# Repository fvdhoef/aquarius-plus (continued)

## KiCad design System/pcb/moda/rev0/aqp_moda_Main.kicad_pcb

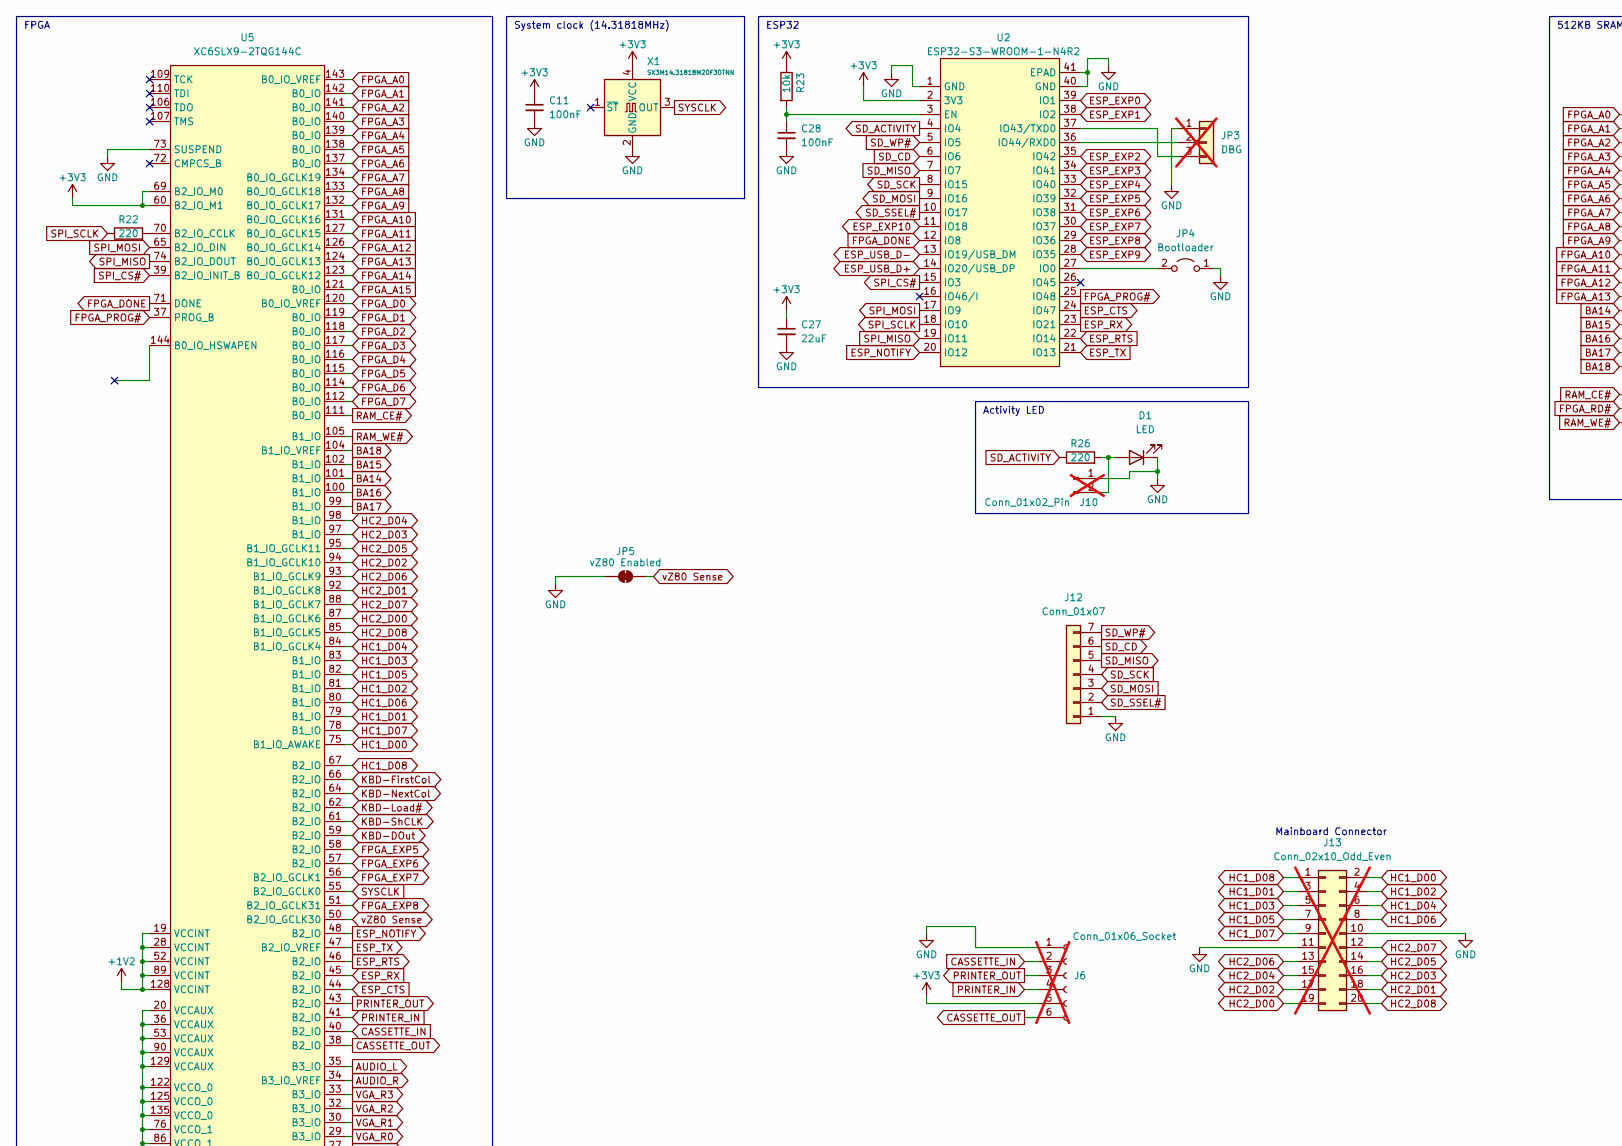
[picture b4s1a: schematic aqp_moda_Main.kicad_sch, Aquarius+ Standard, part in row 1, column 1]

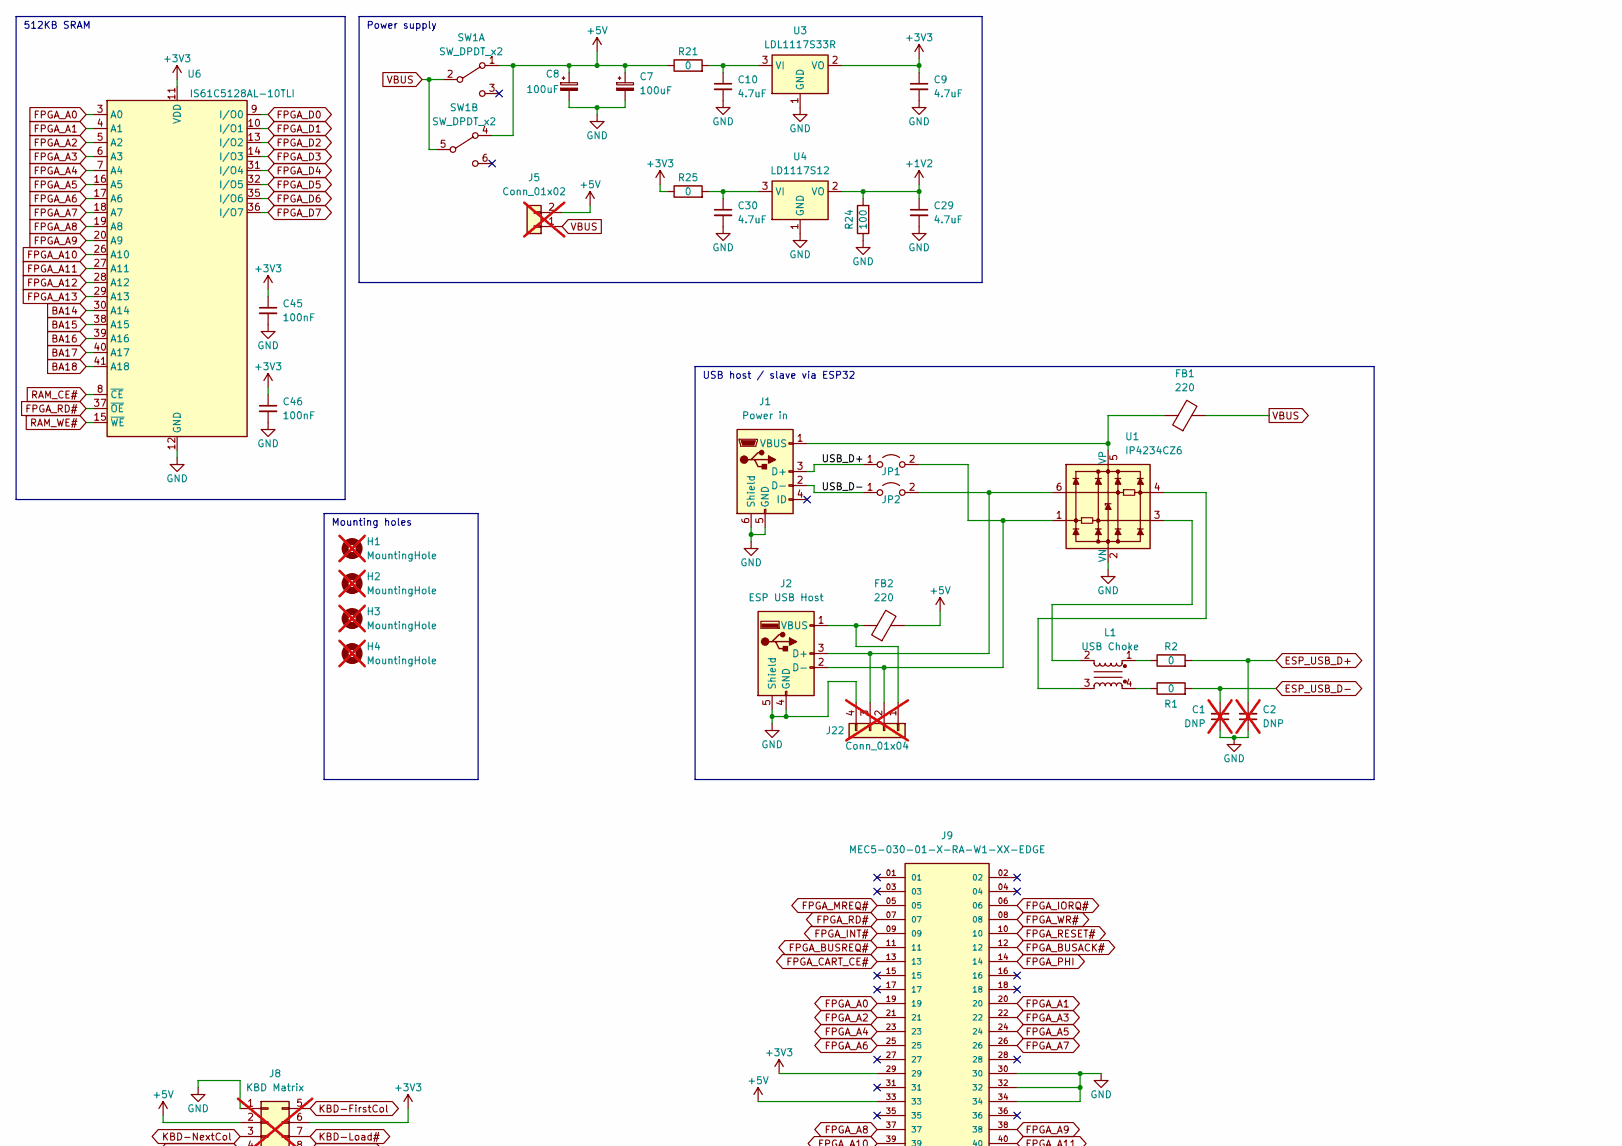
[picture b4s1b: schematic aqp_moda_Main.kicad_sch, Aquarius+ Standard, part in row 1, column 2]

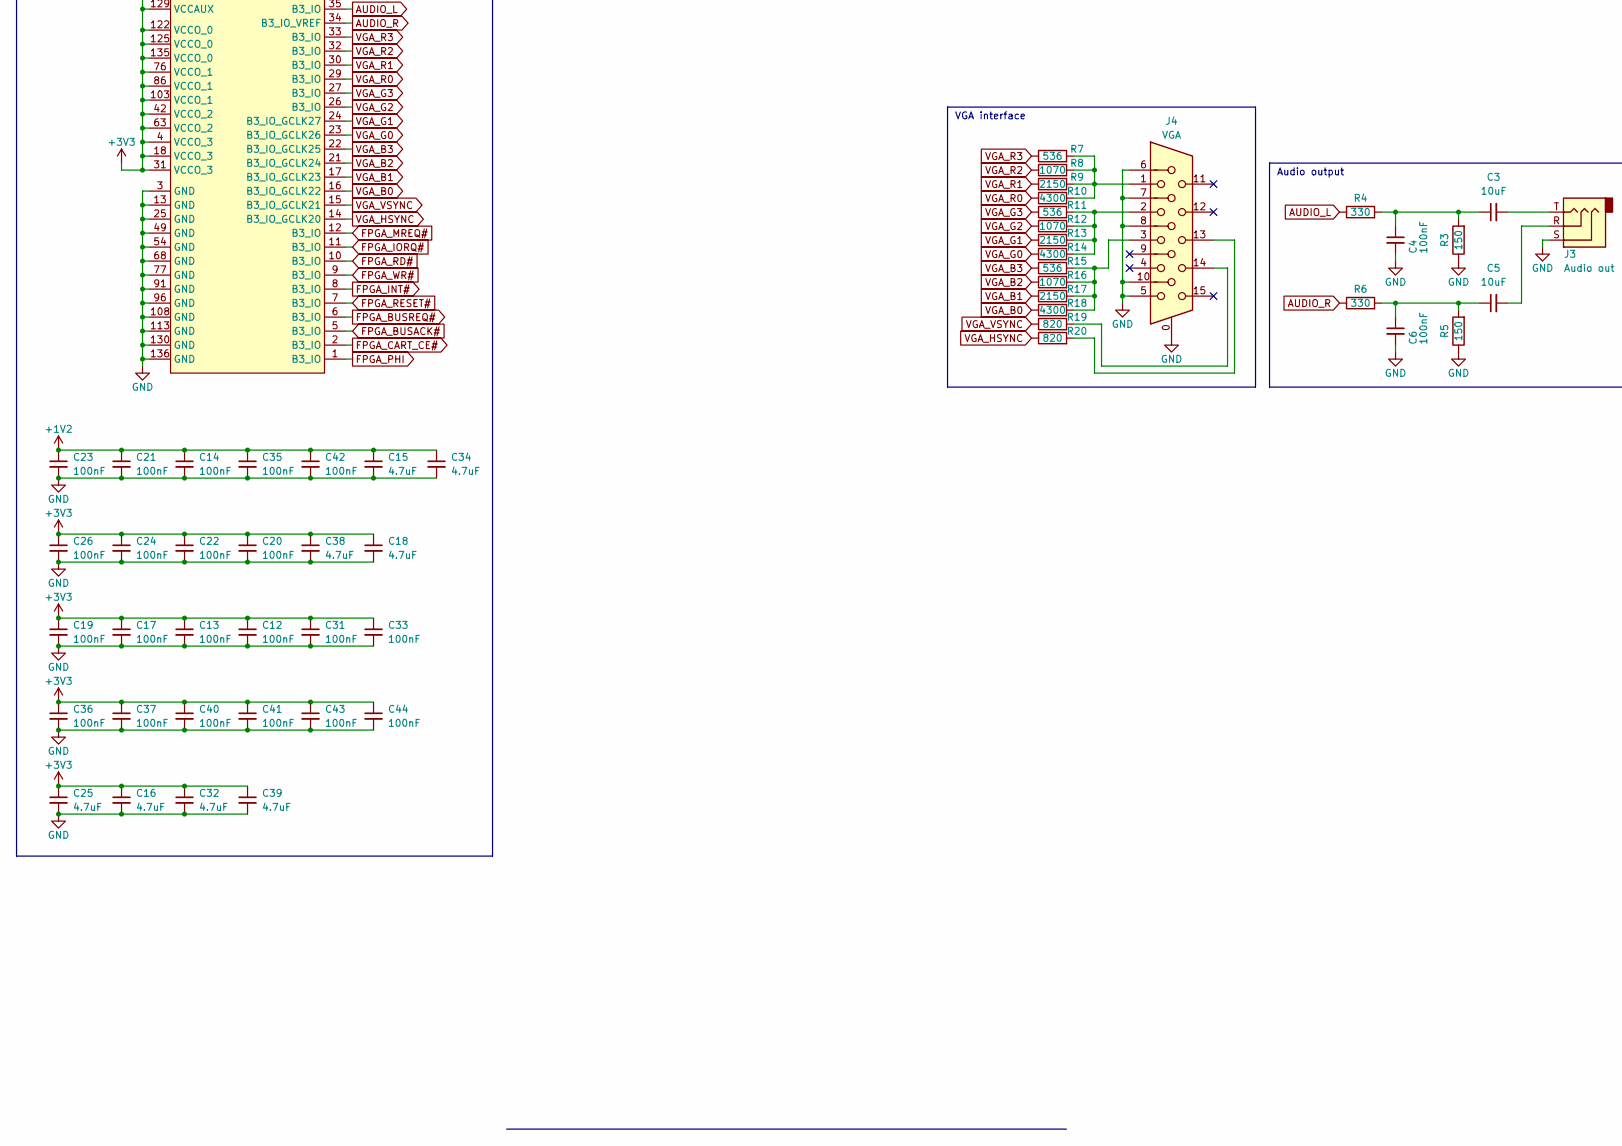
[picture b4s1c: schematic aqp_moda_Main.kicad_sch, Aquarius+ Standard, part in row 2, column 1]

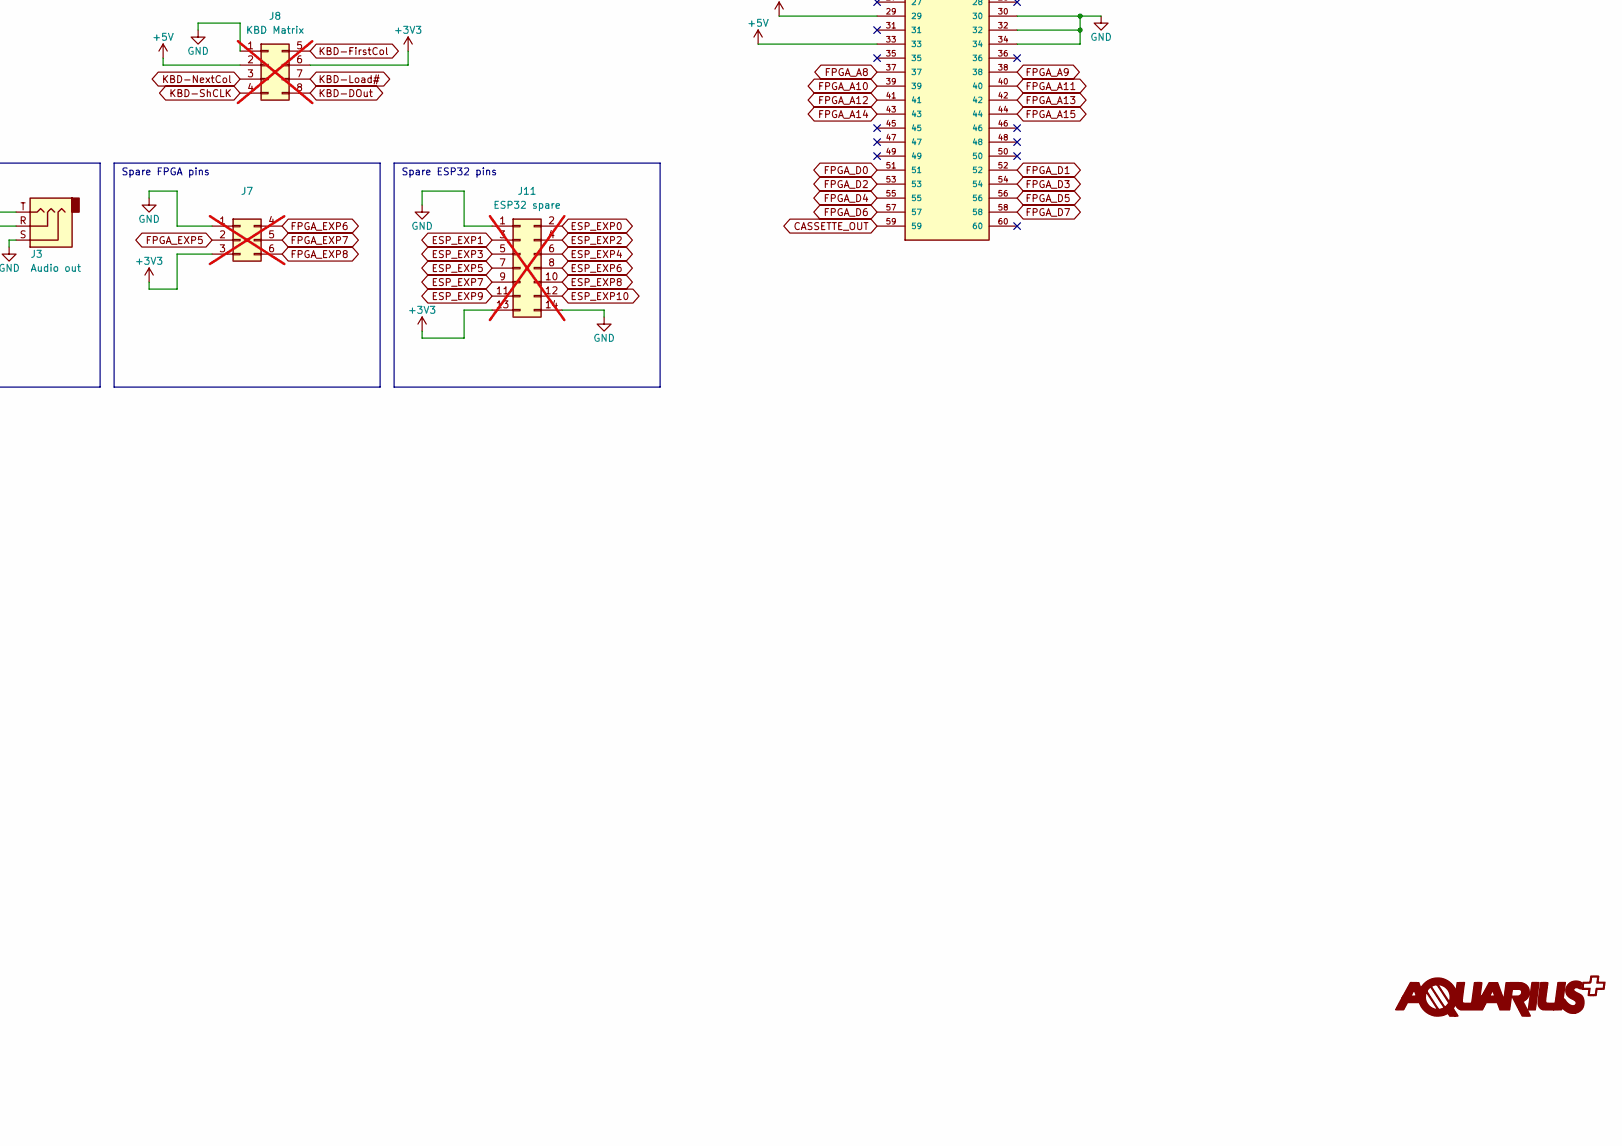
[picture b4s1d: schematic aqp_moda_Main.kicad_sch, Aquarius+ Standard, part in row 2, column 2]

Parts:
C1, C2: DNP; C_0603_1608Metric; not fitted
C3, C5: 10uF; C_0805_2012Metric; JLCPCB C15850
C4, C6, C11, C12, C13, C14, C17, C19, C20, C21, C22, C23, C24, C26, C28, C31, C33, C35, C36, C37, C40, C41, C42, C43, C44, C45, C46: 100nF; C_0603_1608Metric; JLCPCB C14663
C7, C8: 100uF; CP_Elec_6.3x7.7; JLCPCB C264047
C9, C10, C15, C16, C18, C25, C29, C30, C32, C34, C38, C39: 4.7uF; C_0603_1608Metric; JLCPCB C19666
C27: 22uF; C_1206_3216Metric; JLCPCB C12891
D1: LED; LED_0805_2012Metric; JLCPCB C2293
FB1, FB2: 220; L_0603_1608Metric; JLCPCB C2661695
H1, H2, H3, H4: MountingHole; MountingHole_3.2mm_M3; not fitted
J1: Power in; AMPHENOL_10118194-0001LF; JLCPCB C132563
J2: ESP USB Host; USB_A_Molex_67643_Horizontal; JLCPCB C2798029
J3: Audio out; C2939180; JLCPCB C2939180
J4: VGA; ICD15S13E4GV00LF; JLCPCB C138387
J5: Conn_01x02; PinHeader_1x02_P2.54mm_Horizontal; not fitted
J6: Conn_01x06_Socket; PinHeader_1x06_P2.54mm_Vertical; not fitted
J7: Conn_02x03_Top_Bottom; PinSocket_2x03_P2.54mm_Vertical; not fitted
J8: KBD Matrix; PinHeader_2x04_P2.54mm_Vertical; not fitted
J9: MEC5-030-01-X-RA-W1-XX-EDGE; SAMTEC_MEC5-030-01-X-RA-W1-XX-EDGE; PARTREV C
J10: Conn_01x02_Pin; PinHeader_1x02_P2.54mm_Vertical; not fitted
J11: ESP32 spare; PinHeader_2x07_P2.54mm_Vertical; not fitted
J12: Conn_01x07; PinHeader_1x07_P2.54mm_Vertical
J13: Conn_02x10_Odd_Even; IDC-Header_2x10_P2.54mm_Vertical; not fitted
J22: Conn_01x04; PinHeader_1x04_P2.54mm_Vertical; not fitted
JP1, JP2: Pin Header; PinHeader_1x02_P2.54mm_Vertical; JLCPCB C5116481
JP3: DBG; PinHeader_1x03_P2.54mm_Vertical; not fitted
JP4: Bootloader; PinHeader_1x02_P2.54mm_Vertical; JLCPCB C5116481
JP5: vZ80 Enabled; SolderJumper-2_P1.3mm_Bridged_RoundedPad1.0x1.5mm
L1: USB Choke; WE-CNSW_08058; JLCPCB C2649327
R1, R2, R21, R25: 0; R_0603_1608Metric; JLCPCB C2784885
R3, R5: 150; R_0603_1608Metric; JLCPCB C22808
R4, R6: 330; R_0603_1608Metric; JLCPCB C23138
R7, R11, R15: 536; R_0603_1608Metric; JLCPCB C227956
R8, R12, R16: 1070; R_0603_1608Metric; JLCPCB C137783
R9, R13, R17: 2150; R_0603_1608Metric; JLCPCB C170518
R10, R14, R18: 4300; R_0603_1608Metric; JLCPCB C23159
R19, R20: 820; R_0603_1608Metric; JLCPCB C23253
R22, R26: 220; R_0603_1608Metric; JLCPCB C22962
R23: 10k; R_0603_1608Metric; JLCPCB C25804
R24: 100; R_0603_1608Metric; JLCPCB C22775
SW1: SW_DPDT_x2; SW_E-Switch_EG2219_DPDT_Angled; JLCPCB C3664594
U1: IP4234CZ6; SC-74-6_1.55x2.9mm_P0.95mm; JLCPCB C455086
U2: ESP32-S3-WROOM-1-N4R2; ESP32-S2-SOLO-N4R2; JLCPCB C2913203
U3: LDL1117S33R; SOT-223-3_TabPin2; JLCPCB C155612
U4: LD1117S12; SOT-223-3_TabPin2; JLCPCB C155612
U5: XC6SLX9-2TQG144C; TQFP-144_20x20mm_P0.5mm; JLCPCB C27408
U6: IS61C5128AL-10TLI; TSOP-II-44_10.16x18.41mm_P0.8mm
X1: SX3M14.31818M20F30TNN; Oscillator_SMD_SeikoEpson_SG8002CE-4Pin_3.2x2.5mm; JLCPCB C2901565

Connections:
+1V2: C14.1, C15.1, C21.1, C23.1, C29.1, C34.1, C35.1, C42.1, R24.2, U4.2 (VO), U5.19 (VCCINT), U5.28 (VCCINT), U5.52 (VCCINT), U5.89 (VCCINT), U5.128 (VCCINT)
+3V3: C9.1, C11.1, C12.1, C13.1, C16.1, C17.1, C18.1, C19.1, C20.1, C22.1, C24.1, C25.1, C26.1, C27.1, C31.1, C32.1, C33.1, C36.1, C37.1, C38.1, C39.1, C40.1, C41.1, C43.1, C44.1, C45.1, C46.1, J6.5, J7.3, J8.6, J9.29, J11.13, R23.1, R25.1, U2.2 (3V3), U3.2 (VO), U5.4 (VCCO_3), U5.18 (VCCO_3), U5.20 (VCCAUX), U5.31 (VCCO_3), U5.36 (VCCAUX), U5.42 (VCCO_2), U5.53 (VCCAUX), U5.60 (B2_IO_M1), U5.63 (VCCO_2), U5.69 (B2_IO_M0), U5.76 (VCCO_1), U5.86 (VCCO_1), U5.90 (VCCAUX), U5.103 (VCCO_1), U5.122 (VCCO_0), U5.125 (VCCO_0), U5.129 (VCCAUX), U5.135 (VCCO_0), U6.11 (VDD), U6.33 (VDD), X1.4 (VCC)
+5V: C7.1, C8.1, FB2.2, J5.2, J8.2, J9.33, R21.1, SW1.1 (A), SW1.4 (A)
/USB_D+: J1.3 (D+), JP1.1 (A)
/USB_D-: J1.2 (D-), JP2.1 (A)
AUDIO_L: R4.1, U5.35 (B3_IO)
AUDIO_R: R6.1, U5.34 (B3_IO_VREF)
BA14: U5.101 (B1_IO), U6.30 (A14)
BA15: U5.102 (B1_IO), U6.38 (A15)
BA16: U5.100 (B1_IO), U6.39 (A16)
BA17: U5.99 (B1_IO), U6.40 (A17)
BA18: U5.104 (B1_IO_VREF), U6.41 (A18)
CASSETTE_IN: J6.2, U5.40 (B2_IO)
CASSETTE_OUT: J6.6, J9.59, U5.38 (B2_IO)
ESP_CTS: U2.24 (IO47), U5.44 (B2_IO)
ESP_EXP0: J11.2, U2.39 (IO1)
ESP_EXP1: J11.3, U2.38 (IO2)
ESP_EXP2: J11.4, U2.35 (IO42)
ESP_EXP3: J11.5, U2.34 (IO41)
ESP_EXP4: J11.6, U2.33 (IO40)
ESP_EXP5: J11.7, U2.32 (IO39)
ESP_EXP6: J11.8, U2.31 (IO38)
ESP_EXP7: J11.9, U2.30 (IO37)
ESP_EXP8: J11.10, U2.29 (IO36)
ESP_EXP9: J11.11, U2.28 (IO35)
ESP_EXP10: J11.12, U2.11 (IO18)
ESP_NOTIFY: U2.20 (IO12), U5.48 (B2_IO)
ESP_RTS: U2.22 (IO14), U5.46 (B2_IO)
ESP_RX: U2.23 (IO21), U5.45 (B2_IO)
ESP_TX: U2.21 (IO13), U5.47 (B2_IO_VREF)
ESP_USB_D+: C2.2, R2.2, U2.14 (IO20/USB_DP)
ESP_USB_D-: C1.2, R1.2, U2.13 (IO19/USB_DM)
FPGA_A0: J9.19, U5.143 (B0_IO_VREF), U6.3 (A0)
FPGA_A1: J9.20, U5.142 (B0_IO), U6.4 (A1)
FPGA_A2: J9.21, U5.141 (B0_IO), U6.5 (A2)
FPGA_A3: J9.22, U5.140 (B0_IO), U6.6 (A3)
FPGA_A4: J9.23, U5.139 (B0_IO), U6.7 (A4)
FPGA_A5: J9.24, U5.138 (B0_IO), U6.16 (A5)
FPGA_A6: J9.25, U5.137 (B0_IO), U6.17 (A6)
FPGA_A7: J9.26, U5.134 (B0_IO_GCLK19), U6.18 (A7)
FPGA_A8: J9.37, U5.133 (B0_IO_GCLK18), U6.19 (A8)
FPGA_A9: J9.38, U5.132 (B0_IO_GCLK17), U6.20 (A9)
FPGA_A10: J9.39, U5.131 (B0_IO_GCLK16), U6.26 (A10)
FPGA_A11: J9.40, U5.127 (B0_IO_GCLK15), U6.27 (A11)
FPGA_A12: J9.41, U5.126 (B0_IO_GCLK14), U6.28 (A12)
FPGA_A13: J9.42, U5.124 (B0_IO_GCLK13), U6.29 (A13)
FPGA_A14: J9.43, U5.123 (B0_IO_GCLK12)
FPGA_A15: J9.44, U5.121 (B0_IO)
FPGA_BUSACK#: J9.12, U5.5 (B3_IO)
FPGA_BUSREQ#: J9.11, U5.6 (B3_IO)
FPGA_CART_CE#: J9.13, U5.2 (B3_IO)
FPGA_D0: J9.51, U5.120 (B0_IO_VREF), U6.9 (I/O0)
FPGA_D1: J9.52, U5.119 (B0_IO), U6.10 (I/O1)
FPGA_D2: J9.53, U5.118 (B0_IO), U6.13 (I/O2)
FPGA_D3: J9.54, U5.117 (B0_IO), U6.14 (I/O3)
FPGA_D4: J9.55, U5.116 (B0_IO), U6.31 (I/O4)
FPGA_D5: J9.56, U5.115 (B0_IO), U6.32 (I/O5)
FPGA_D6: J9.57, U5.114 (B0_IO), U6.35 (I/O6)
FPGA_D7: J9.58, U5.112 (B0_IO), U6.36 (I/O7)
FPGA_DONE: U2.12 (IO8), U5.71 (DONE)
FPGA_EXP5: J7.2, U5.58 (B2_IO)
FPGA_EXP6: J7.4, U5.57 (B2_IO)
FPGA_EXP7: J7.5, U5.56 (B2_IO_GCLK1)
FPGA_EXP8: J7.6, U5.51 (B2_IO_GCLK31)
FPGA_INT#: J9.09, U5.8 (B3_IO)
FPGA_IORQ#: J9.06, U5.11 (B3_IO)
FPGA_MREQ#: J9.05, U5.12 (B3_IO)
FPGA_PHI: J9.14, U5.1 (B3_IO)
FPGA_PROG#: U2.25 (IO48), U5.37 (PROG_B)
FPGA_RD#: J9.07, U5.10 (B3_IO), U6.37 (~OE)
FPGA_RESET#: J9.10, U5.7 (B3_IO)
FPGA_WR#: J9.08, U5.9 (B3_IO)
GND: C1.1, C2.1, C4.2, C6.2, C7.2, C8.2, C9.2, C10.2, C11.2, C12.2, C13.2, C14.2, C15.2, C16.2, C17.2, C18.2, C19.2, C20.2, C21.2, C22.2, C23.2, C24.2, C25.2, C26.2, C27.2, C28.2, C29.2, C30.2, C31.2, C32.2, C33.2, C34.2, C35.2, C36.2, C37.2, C38.2, C39.2, C40.2, C41.2, C42.2, C43.2, C44.2, C45.2, C46.2, D1.1 (K), J1.5 (GND), J1.6 (Shield), J2.4 (GND), J2.5 (Shield), J3.S, J4.0, J4.5, J4.6, J4.7, J4.8, J4.10, J6.1, J7.1, J8.1, J9.30, J9.32, J9.34, J10.1, J11.1, J11.14, J12.1, J13.10, J13.11, J22.4, JP3.1, JP4.1 (A), JP5.1 (A), R3.1, R5.1, R24.1, U1.2 (VN), U2.1 (GND), U2.40 (GND), U2.41 (EPAD), U3.1 (GND), U4.1 (GND), U5.3 (GND), U5.13 (GND), U5.25 (GND), U5.49 (GND), U5.54 (GND), U5.68 (GND), U5.73 (SUSPEND), U5.77 (GND), U5.91 (GND), U5.96 (GND), U5.108 (GND), U5.113 (GND), U5.130 (GND), U5.136 (GND), U6.12 (GND), U6.34 (GND), X1.2 (GND)
HC1_D00: J13.2, U5.75 (B1_IO_AWAKE)
HC1_D01: J13.3, U5.79 (B1_IO)
HC1_D02: J13.4, U5.81 (B1_IO)
HC1_D03: J13.5, U5.83 (B1_IO)
HC1_D04: J13.6, U5.84 (B1_IO_GCLK4)
HC1_D05: J13.7, U5.82 (B1_IO)
HC1_D06: J13.8, U5.80 (B1_IO)
HC1_D07: J13.9, U5.78 (B1_IO)
HC1_D08: J13.1, U5.67 (B2_IO)
HC2_D00: J13.19, U5.87 (B1_IO_GCLK6)
HC2_D01: J13.18, U5.92 (B1_IO_GCLK8)
HC2_D02: J13.17, U5.94 (B1_IO_GCLK10)
HC2_D03: J13.16, U5.97 (B1_IO)
HC2_D04: J13.15, U5.98 (B1_IO)
HC2_D05: J13.14, U5.95 (B1_IO_GCLK11)
HC2_D06: J13.13, U5.93 (B1_IO_GCLK9)
HC2_D07: J13.12, U5.88 (B1_IO_GCLK7)
HC2_D08: J13.20, U5.85 (B1_IO_GCLK5)
KBD-DOut: J8.8, U5.59 (B2_IO)
KBD-FirstCol: J8.5, U5.66 (B2_IO)
KBD-Load#: J8.7, U5.62 (B2_IO)
KBD-NextCol: J8.3, U5.64 (B2_IO)
KBD-ShCLK: J8.4, U5.61 (B2_IO)
unnamed: C3.1, C4.1, R3.2, R4.2
unnamed: C3.2, J3.T
unnamed: C5.1, C6.1, R5.2, R6.2
unnamed: C5.2, J3.R
unnamed: D1.2 (A), J10.2, R26.2
unnamed: FB1.1, J1.1 (VBUS), U1.5 (VP)
unnamed: J2.3 (D+), J22.3, JP2.2 (B), U1.6
unnamed: J2.2 (D-), J22.2, JP1.2 (B), U1.1
unnamed: FB2.1, J2.1 (VBUS), J22.1
unnamed: J4.1, R7.2, R8.2, R9.2, R10.2
unnamed: J4.2, R11.2, R12.2, R13.2, R14.2
unnamed: J4.3, R15.2, R16.2, R17.2, R18.2
unnamed: J4.13, R20.2
unnamed: J4.14, R19.2
unnamed: JP3.2, U2.36 (IO44/RXD0)
unnamed: JP3.3, U2.37 (IO43/TXD0)
unnamed: JP4.2 (B), U2.27 (IO0)
unnamed: L1.1, R2.1
unnamed: L1.2, U1.3
unnamed: L1.3, U1.4
unnamed: L1.4, R1.1
unnamed: C28.1, R23.2, U2.3 (EN)
unnamed: C10.1, R21.2, U3.3 (VI)
unnamed: C30.1, R25.2, U4.3 (VI)
unnamed: R22.2, U5.70 (B2_IO_CCLK)
PRINTER_IN: J6.4, U5.41 (B2_IO)
PRINTER_OUT: J6.3, U5.43 (B2_IO)
RAM_CE#: U5.111 (B0_IO), U6.8 (~CE)
RAM_WE#: U5.105 (B1_IO), U6.15 (~WE)
SD_ACTIVITY: R26.1, U2.4 (IO4)
SD_CD: J12.6, U2.6 (IO6)
SD_MISO: J12.5, U2.7 (IO7)
SD_MOSI: J12.3, U2.9 (IO16)
SD_SCK: J12.4, U2.8 (IO15)
SD_SSEL#: J12.2, U2.10 (IO17)
SD_WP#: J12.7, U2.5 (IO5)
SPI_CS#: U2.15 (IO3), U5.39 (B2_IO_INIT_B)
SPI_MISO: U2.19 (IO11), U5.74 (B2_IO_DOUT)
SPI_MOSI: U2.17 (IO9), U5.65 (B2_IO_DIN)
SPI_SCLK: R22.1, U2.18 (IO10)
SYSCLK: U5.55 (B2_IO_GCLK0), X1.3 (OUT)
VBUS: FB1.2, J5.1, SW1.2 (B), SW1.5 (B)
VGA_B0: R18.1, U5.16 (B3_IO_GCLK22)
VGA_B1: R17.1, U5.17 (B3_IO_GCLK23)
VGA_B2: R16.1, U5.21 (B3_IO_GCLK24)
VGA_B3: R15.1, U5.22 (B3_IO_GCLK25)
VGA_G0: R14.1, U5.23 (B3_IO_GCLK26)
VGA_G1: R13.1, U5.24 (B3_IO_GCLK27)
VGA_G2: R12.1, U5.26 (B3_IO)
VGA_G3: R11.1, U5.27 (B3_IO)
VGA_HSYNC: R20.1, U5.14 (B3_IO_GCLK20)
VGA_R0: R10.1, U5.29 (B3_IO)
VGA_R1: R9.1, U5.30 (B3_IO)
VGA_R2: R8.1, U5.32 (B3_IO)
VGA_R3: R7.1, U5.33 (B3_IO)
VGA_VSYNC: R19.1, U5.15 (B3_IO_GCLK21)
vZ80 Sense: JP5.2 (B), U5.50 (B2_IO_GCLK30)

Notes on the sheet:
System clock (14.31818MHz)
USB host / slave via ESP32
Audio output
Activity LED
Power supply
Spare FPGA pins
ESP32
Mainboard Connector
512KB SRAM
FPGA
Spare ESP32 pins
VGA interface
Mounting holes

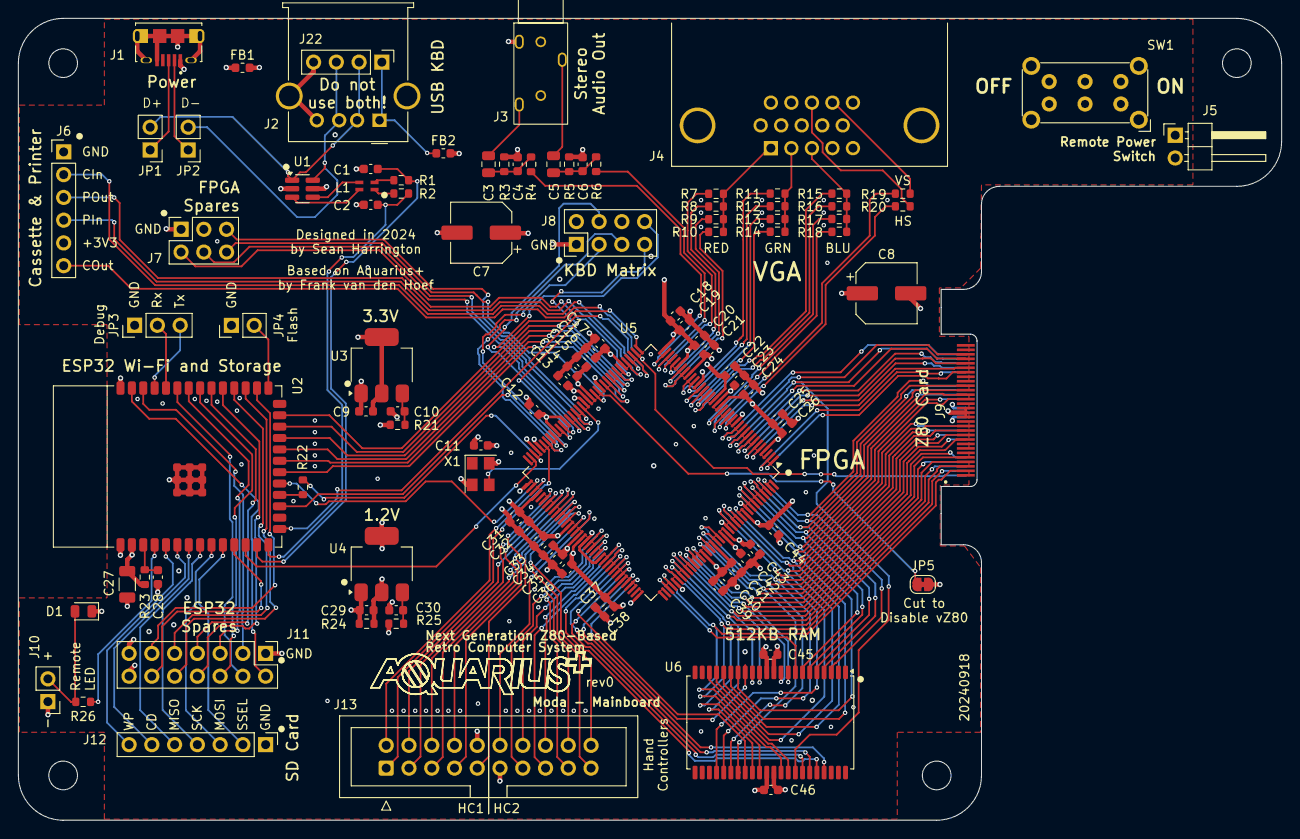
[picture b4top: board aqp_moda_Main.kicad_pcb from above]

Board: 4 copper layers, 141.0 x 89.5 mm, 107 parts (0 on the bottom side), 153 nets.

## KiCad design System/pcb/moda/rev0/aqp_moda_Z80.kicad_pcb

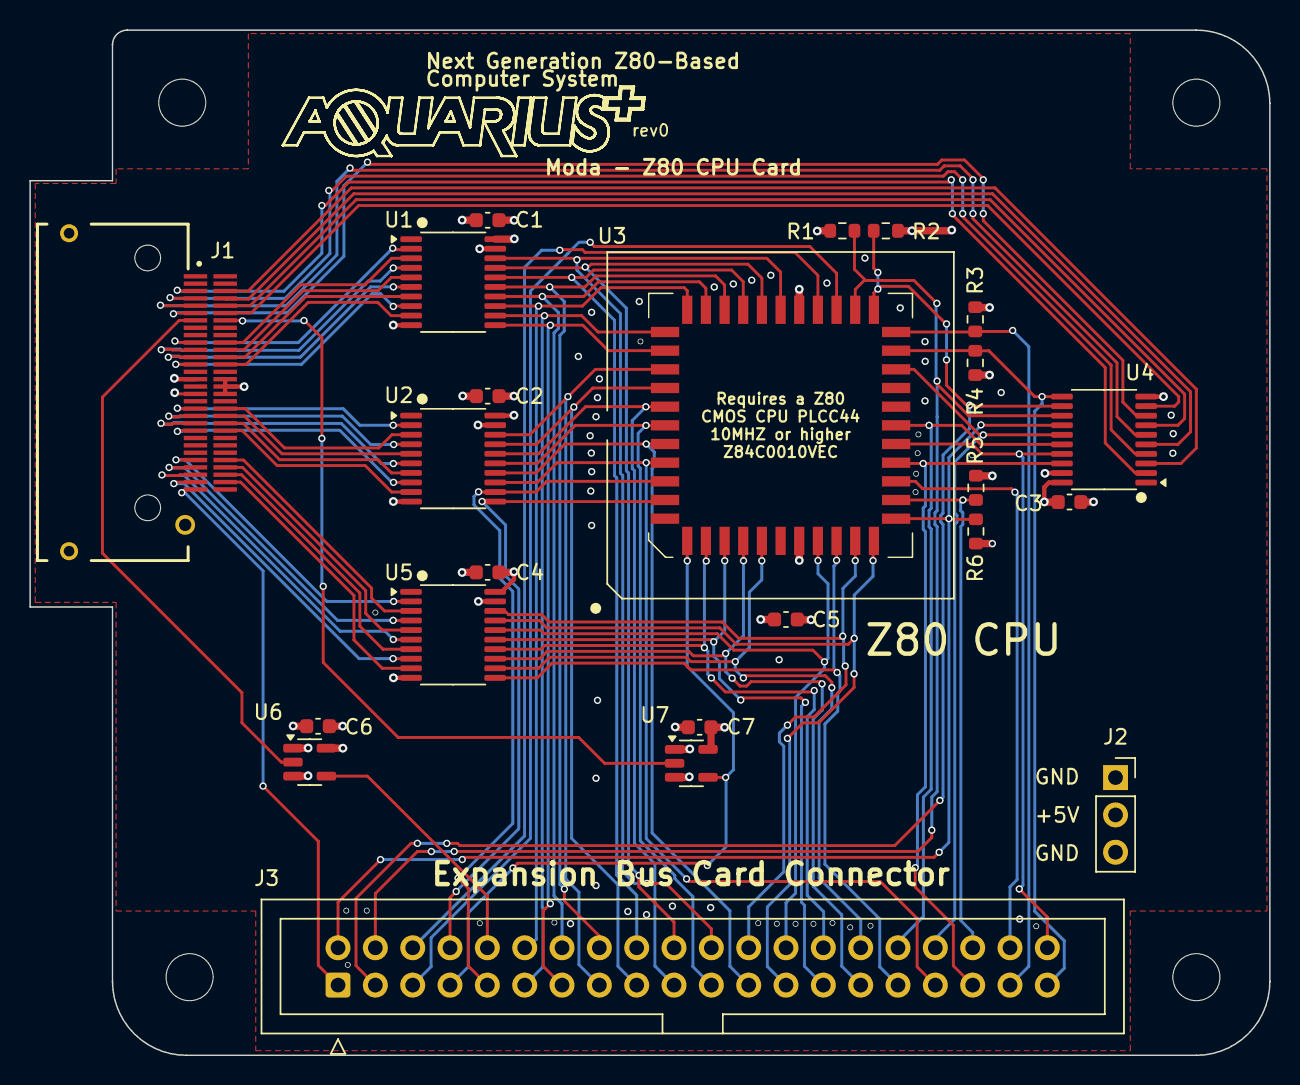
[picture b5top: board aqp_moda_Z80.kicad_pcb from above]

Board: 4 copper layers, 84.3 x 69.8 mm, 27 parts (0 on the bottom side), 77 nets.

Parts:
C1, C2, C3, C4, C5, C6, C7: 100nF; C_0603_1608Metric
H1, H2, H3, H4: MountingHole; MountingHole_3.2mm_M3
J1: MEC5-030-01-X-RA-W1-XX-SOCKET; SAMTEC_MEC5-030-01-X-RA-W1-XX
J2: Conn_01x03; PinSocket_1x03_P2.54mm_Vertical
J3: IDC_02x20; IDC-Header_2x20_P2.54mm_Vertical
R1, R2, R3, R4, R5, R6: 1k; R_0603_1608Metric
U1, U2, U4, U5: SN74CB3T3245PWR; TSSOP-20_4.4x6.5mm_P0.65mm
U3: PLCC-44 SMD Socket; PLCC-44_SMD-Socket
U6, U7: SN74AHCT1G125DBVR; SOT-23-5

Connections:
+3V3: C1.1, C2.1, C3.1, C4.1, J1.29, U1.20 (VCC), U2.20 (VCC), U4.20 (VCC), U5.20 (VCC)
+5V: C5.1, C6.1, C7.1, J1.33, J2.2, R1.1, R2.1, R3.1, R4.1, R5.1, R6.1, U3.13 (+5V), U6.5 (VCC), U7.5 (VCC)
A0: J3.22, U1.18 (B1), U3.34 (A0)
A1: J3.20, U1.17 (B2), U3.35 (A1)
A2: J3.18, U1.16 (B3), U3.36 (A2)
A3: J3.16, U1.15 (B4), U3.37 (A3)
A4: J3.14, U1.14 (B5), U3.38 (A4)
A5: J3.12, U1.13 (B6), U3.39 (A5)
A6: J3.11, U1.12 (B7), U3.40 (A6)
A7: J3.13, U1.11 (B8), U3.41 (A7)
A8: J3.15, U2.18 (B1), U3.42 (A8)
A9: J3.17, U2.17 (B2), U3.43 (A9)
A10: J3.19, U2.16 (B3), U3.44 (A10)
A11: J3.21, U2.15 (B4), U3.1 (A11)
A12: J3.23, U2.14 (B5), U3.2 (A12)
A13: J3.33, U2.13 (B6), U3.3 (A13)
A14: J3.9, U2.12 (B7), U3.4 (A14)
A15: J3.8, U2.11 (B8), U3.5 (A15)
BUSACK#: J3.39, R4.2, U3.27 (~BUSACK), U4.11 (B8)
BUSREQ#: J3.3, R2.2, U3.29 (~BUSREQ), U4.12 (B7)
CART_CE#: J3.10, U6.4
CASSETTE_OUT: J1.59, J3.1
D0: J3.24, U3.16 (D0), U5.18 (B1)
D1: J3.25, U3.17 (D1), U5.17 (B2)
D2: J3.26, U3.14 (D2), U5.16 (B3)
D3: J3.27, U3.9 (D3), U5.15 (B4)
D4: J3.28, U3.8 (D4), U5.14 (B5)
D5: J3.29, U3.10 (D5), U5.13 (B6)
D6: J3.30, U3.11 (D6), U5.12 (B7)
D7: J3.31, U3.15 (D7), U5.11 (B8)
FPGA_A0: J1.19, U1.2 (A1)
FPGA_A1: J1.20, U1.3 (A2)
FPGA_A2: J1.21, U1.4 (A3)
FPGA_A3: J1.22, U1.5 (A4)
FPGA_A4: J1.23, U1.6 (A5)
FPGA_A5: J1.24, U1.7 (A6)
FPGA_A6: J1.25, U1.8 (A7)
FPGA_A7: J1.26, U1.9 (A8)
FPGA_A8: J1.37, U2.2 (A1)
FPGA_A9: J1.38, U2.3 (A2)
FPGA_A10: J1.39, U2.4 (A3)
FPGA_A11: J1.40, U2.5 (A4)
FPGA_A12: J1.41, U2.6 (A5)
FPGA_A13: J1.42, U2.7 (A6)
FPGA_A14: J1.43, U2.8 (A7)
FPGA_A15: J1.44, U2.9 (A8)
FPGA_BUSACK#: J1.12, U4.9 (A8)
FPGA_BUSREQ#: J1.11, U4.8 (A7)
FPGA_CART_CE#: J1.13, U6.2
FPGA_D0: J1.51, U5.2 (A1)
FPGA_D1: J1.52, U5.3 (A2)
FPGA_D2: J1.53, U5.4 (A3)
FPGA_D3: J1.54, U5.5 (A4)
FPGA_D4: J1.55, U5.6 (A5)
FPGA_D5: J1.56, U5.7 (A6)
FPGA_D6: J1.57, U5.8 (A7)
FPGA_D7: J1.58, U5.9 (A8)
FPGA_INT#: J1.09, U4.6 (A5)
FPGA_IORQ#: J1.06, U4.3 (A2)
FPGA_MREQ#: J1.05, U4.2 (A1)
FPGA_PHI: J1.14, U7.2
FPGA_RD#: J1.07, U4.4 (A3)
FPGA_RESET#: J1.10, U4.7 (A6)
FPGA_WR#: J1.08, U4.5 (A4)
GND: C1.2, C2.2, C3.2, C4.2, C5.2, C6.2, C7.2, J1.30, J1.32, J1.34, J2.1, J2.3, U1.10 (GND), U1.19 (~OE), U2.10 (GND), U2.19 (~OE), U3.33 (GND), U4.10 (GND), U4.19 (~OE), U5.10 (GND), U5.19 (~OE), U6.1, U6.3 (GND), U7.1, U7.3 (GND)
HALT#: J3.38, U3.20 (~HALT)
INT#: J3.2, R6.2, U3.18 (~INT), U4.14 (B5)
IORQ#: J3.40, U3.22 (~IORQ), U4.17 (B2)
M1#: J3.5, U3.31 (~M1)
MREQ#: J3.35, U3.21 (~MREQ), U4.18 (B1)
NMI#: J3.36, R5.2, U3.19 (~NMI)
PHI: J3.7, U3.7 (CLK), U7.4
RD#: J3.32, U3.23 (~RD), U4.16 (B3)
RESET#: J3.4, R1.2, U3.30 (~RESET), U4.13 (B6)
RFSH#: J3.6, U3.32 (~RFSH)
WAIT#: J3.37, R3.2, U3.28 (~WAIT)
WR#: J3.34, U3.26 (~WR), U4.15 (B4)

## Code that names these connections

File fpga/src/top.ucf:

NET "sysclk"            LOC = P55;
NET "ebus_reset_n"      LOC = P7;
NET "ebus_phi"          LOC = P1;
NET "ebus_a[0]"         LOC = P143;
NET "ebus_a[1]"         LOC = P142;
NET "ebus_a[2]"         LOC = P141;
NET "ebus_a[3]"         LOC = P140;
NET "ebus_a[4]"         LOC = P139;
NET "ebus_a[5]"         LOC = P138;
NET "ebus_a[6]"         LOC = P137;
NET "ebus_a[7]"         LOC = P134;
NET "ebus_a[8]"         LOC = P133;
NET "ebus_a[9]"         LOC = P132;
NET "ebus_a[10]"        LOC = P131;
NET "ebus_a[11]"        LOC = P127;
NET "ebus_a[12]"        LOC = P126;
NET "ebus_a[13]"        LOC = P124;
NET "ebus_a[14]"        LOC = P123;
NET "ebus_a[15]"        LOC = P121;
NET "ebus_d[0]"         LOC = P120;
NET "ebus_d[1]"         LOC = P119;
NET "ebus_d[2]"         LOC = P118;
NET "ebus_d[3]"         LOC = P117;
NET "ebus_d[4]"         LOC = P116;
NET "ebus_d[5]"         LOC = P115;
NET "ebus_d[6]"         LOC = P114;
NET "ebus_d[7]"         LOC = P112;
NET "ebus_rd_n"         LOC = P10;
NET "ebus_wr_n"         LOC = P9;
NET "ebus_mreq_n"       LOC = P12;
NET "ebus_iorq_n"       LOC = P11;
NET "ebus_int_n"        LOC = P8;
NET "ebus_busreq_n"     LOC = P6;
NET "ebus_busack_n"     LOC = P5;
NET "ebus_ba[0]"        LOC = P104;
NET "ebus_ba[1]"        LOC = P102;
NET "ebus_ba[2]"        LOC = P101;
NET "ebus_ba[3]"        LOC = P100;
NET "ebus_ba[4]"        LOC = P99;
NET "ebus_ram_ce_n"     LOC = P111;
NET "ebus_cart_ce_n"    LOC = P2;
NET "ebus_ram_we_n"     LOC = P105;
NET "audio_l"           LOC = P35;
NET "audio_r"           LOC = P34;
NET "cassette_out"      LOC = P38;
NET "cassette_in"       LOC = P40;
NET "printer_out"       LOC = P43;
NET "printer_in"        LOC = P41;
NET "exp[0]"            LOC = P66;
NET "exp[1]"            LOC = P64;
NET "exp[2]"            LOC = P62;
NET "exp[3]"            LOC = P61;
NET "exp[4]"            LOC = P59;
NET "exp[5]"            LOC = P58;
NET "exp[6]"            LOC = P57;
NET "exp[7]"            LOC = P56;
NET "exp[8]"            LOC = P51;
NET "exp[9]"            LOC = P50;
NET "vga_r[0]"          LOC = P29;
NET "vga_r[1]"          LOC = P30;
NET "vga_r[2]"          LOC = P32;
NET "vga_r[3]"          LOC = P33;
NET "vga_g[0]"          LOC = P23;
NET "vga_g[1]"          LOC = P24;
NET "vga_g[2]"          LOC = P26;
NET "vga_g[3]"          LOC = P27;
NET "vga_b[0]"          LOC = P16;
NET "vga_b[1]"          LOC = P17;
NET "vga_b[2]"          LOC = P21;
NET "vga_b[3]"          LOC = P22;
NET "vga_hsync"         LOC = P14;
NET "vga_vsync"         LOC = P15;
NET "esp_tx"            LOC = P47;
NET "esp_rx"            LOC = P45;
NET "esp_rts"           LOC = P46;
NET "esp_cts"           LOC = P44;
NET "esp_ssel_n"        LOC = P74;
NET "esp_sclk"          LOC = P70;
NET "esp_mosi"          LOC = P65;
NET "esp_miso"          LOC = P39;
NET "esp_notify"        LOC = P48;
NET "hc1[0]"            LOC = P75;
NET "hc1[1]"            LOC = P79;
NET "hc1[2]"            LOC = P81;
NET "hc1[3]"            LOC = P83;
NET "hc1[4]"            LOC = P84;
NET "hc1[5]"            LOC = P82;
NET "hc1[6]"            LOC = P80;
NET "hc1[7]"            LOC = P78;
NET "hc1[8]"            LOC = P67;
NET "hc2[0]"            LOC = P87;
NET "hc2[1]"            LOC = P92;
NET "hc2[2]"            LOC = P94;
NET "hc2[3]"            LOC = P97;
NET "hc2[4]"            LOC = P98;
NET "hc2[5]"            LOC = P95;
NET "hc2[6]"            LOC = P93;
NET "hc2[7]"            LOC = P88;
NET "hc2[8]"            LOC = P85;

NET "hc1[0]" PULLUP;
NET "hc1[1]" PULLUP;
NET "hc1[2]" PULLUP;
NET "hc1[3]" PULLUP;
NET "hc1[4]" PULLUP;
NET "hc1[5]" PULLUP;
NET "hc1[6]" PULLUP;
NET "hc1[7]" PULLUP;

NET "hc2[0]" PULLUP;
NET "hc2[1]" PULLUP;
NET "hc2[2]" PULLUP;
NET "hc2[3]" PULLUP;
NET "hc2[4]" PULLUP;
NET "hc2[5]" PULLUP;
NET "hc2[6]" PULLUP;
NET "hc2[7]" PULLUP;

NET "sysclk"            IOSTANDARD = LVTTL;
NET "ebus_reset_n"      IOSTANDARD = LVTTL;
NET "ebus_phi"          IOSTANDARD = LVTTL;
NET "ebus_a[0]"         IOSTANDARD = LVTTL;
NET "ebus_a[1]"         IOSTANDARD = LVTTL;
NET "ebus_a[2]"         IOSTANDARD = LVTTL;
NET "ebus_a[3]"         IOSTANDARD = LVTTL;
NET "ebus_a[4]"         IOSTANDARD = LVTTL;
NET "ebus_a[5]"         IOSTANDARD = LVTTL;
NET "ebus_a[6]"         IOSTANDARD = LVTTL;
NET "ebus_a[7]"         IOSTANDARD = LVTTL;
NET "ebus_a[8]"         IOSTANDARD = LVTTL;
NET "ebus_a[9]"         IOSTANDARD = LVTTL;
NET "ebus_a[10]"        IOSTANDARD = LVTTL;
NET "ebus_a[11]"        IOSTANDARD = LVTTL;
NET "ebus_a[12]"        IOSTANDARD = LVTTL;
NET "ebus_a[13]"        IOSTANDARD = LVTTL;
NET "ebus_a[14]"        IOSTANDARD = LVTTL;
NET "ebus_a[15]"        IOSTANDARD = LVTTL;
NET "ebus_d[0]"         IOSTANDARD = LVTTL;
NET "ebus_d[1]"         IOSTANDARD = LVTTL;
NET "ebus_d[2]"         IOSTANDARD = LVTTL;
NET "ebus_d[3]"         IOSTANDARD = LVTTL;
NET "ebus_d[4]"         IOSTANDARD = LVTTL;
NET "ebus_d[5]"         IOSTANDARD = LVTTL;
NET "ebus_d[6]"         IOSTANDARD = LVTTL;
NET "ebus_d[7]"         IOSTANDARD = LVTTL;
NET "ebus_rd_n"         IOSTANDARD = LVTTL;
NET "ebus_wr_n"         IOSTANDARD = LVTTL;
NET "ebus_mreq_n"       IOSTANDARD = LVTTL;
NET "ebus_iorq_n"       IOSTANDARD = LVTTL;
NET "ebus_int_n"        IOSTANDARD = LVTTL;
NET "ebus_busreq_n"     IOSTANDARD = LVTTL;
NET "ebus_busack_n"     IOSTANDARD = LVTTL;
NET "ebus_ba[0]"        IOSTANDARD = LVTTL;
NET "ebus_ba[1]"        IOSTANDARD = LVTTL;
NET "ebus_ba[2]"        IOSTANDARD = LVTTL;
NET "ebus_ba[3]"        IOSTANDARD = LVTTL;
NET "ebus_ba[4]"        IOSTANDARD = LVTTL;
NET "ebus_ram_ce_n"     IOSTANDARD = LVTTL;
NET "ebus_cart_ce_n"    IOSTANDARD = LVTTL;
NET "ebus_ram_we_n"     IOSTANDARD = LVTTL;
NET "audio_l"           IOSTANDARD = LVTTL;
NET "audio_r"           IOSTANDARD = LVTTL;
NET "cassette_out"      IOSTANDARD = LVTTL;
NET "cassette_in"       IOSTANDARD = LVTTL;
NET "printer_out"       IOSTANDARD = LVTTL;
NET "printer_in"        IOSTANDARD = LVTTL;
NET "exp[0]"            IOSTANDARD = LVTTL;
NET "exp[1]"            IOSTANDARD = LVTTL;
NET "exp[2]"            IOSTANDARD = LVTTL;
NET "exp[3]"            IOSTANDARD = LVTTL;
NET "exp[4]"            IOSTANDARD = LVTTL;
NET "exp[5]"            IOSTANDARD = LVTTL;
NET "exp[6]"            IOSTANDARD = LVTTL;
NET "exp[7]"            IOSTANDARD = LVTTL;
NET "exp[8]"            IOSTANDARD = LVTTL;
NET "exp[9]"            IOSTANDARD = LVTTL;
NET "vga_r[0]"          IOSTANDARD = LVTTL;
NET "vga_r[1]"          IOSTANDARD = LVTTL;
NET "vga_r[2]"          IOSTANDARD = LVTTL;
NET "vga_r[3]"          IOSTANDARD = LVTTL;
NET "vga_g[0]"          IOSTANDARD = LVTTL;
NET "vga_g[1]"          IOSTANDARD = LVTTL;
NET "vga_g[2]"          IOSTANDARD = LVTTL;
NET "vga_g[3]"          IOSTANDARD = LVTTL;
NET "vga_b[0]"          IOSTANDARD = LVTTL;
NET "vga_b[1]"          IOSTANDARD = LVTTL;
NET "vga_b[2]"          IOSTANDARD = LVTTL;
NET "vga_b[3]"          IOSTANDARD = LVTTL;
NET "vga_hsync"         IOSTANDARD = LVTTL;
NET "vga_vsync"         IOSTANDARD = LVTTL;
NET "esp_tx"            IOSTANDARD = LVTTL;
NET "esp_rx"            IOSTANDARD = LVTTL;
NET "esp_rts"           IOSTANDARD = LVTTL;
NET "esp_cts"           IOSTANDARD = LVTTL;
NET "esp_ssel_n"        IOSTANDARD = LVTTL;
NET "esp_sclk"          IOSTANDARD = LVTTL;
NET "esp_mosi"          IOSTANDARD = LVTTL;
NET "esp_miso"          IOSTANDARD = LVTTL;
NET "esp_notify"        IOSTANDARD = LVTTL;
NET "hc1[0]"            IOSTANDARD = LVTTL;
NET "hc1[1]"            IOSTANDARD = LVTTL;
NET "hc1[2]"            IOSTANDARD = LVTTL;
NET "hc1[3]"            IOSTANDARD = LVTTL;
NET "hc1[4]"            IOSTANDARD = LVTTL;
NET "hc1[5]"            IOSTANDARD = LVTTL;
NET "hc1[6]"            IOSTANDARD = LVTTL;
NET "hc1[7]"            IOSTANDARD = LVTTL;
NET "hc1[8]"            IOSTANDARD = LVTTL;
NET "hc2[0]"            IOSTANDARD = LVTTL;
NET "hc2[1]"            IOSTANDARD = LVTTL;
NET "hc2[2]"            IOSTANDARD = LVTTL;
NET "hc2[3]"            IOSTANDARD = LVTTL;
NET "hc2[4]"            IOSTANDARD = LVTTL;
NET "hc2[5]"            IOSTANDARD = LVTTL;
NET "hc2[6]"            IOSTANDARD = LVTTL;
NET "hc2[7]"            IOSTANDARD = LVTTL;
NET "hc2[8]"            IOSTANDARD = LVTTL;

NET "sysclk" TNM_NET = sysclk;
TIMESPEC TS_sysclk = PERIOD "sysclk" 14.31818 MHz HIGH 50%;
